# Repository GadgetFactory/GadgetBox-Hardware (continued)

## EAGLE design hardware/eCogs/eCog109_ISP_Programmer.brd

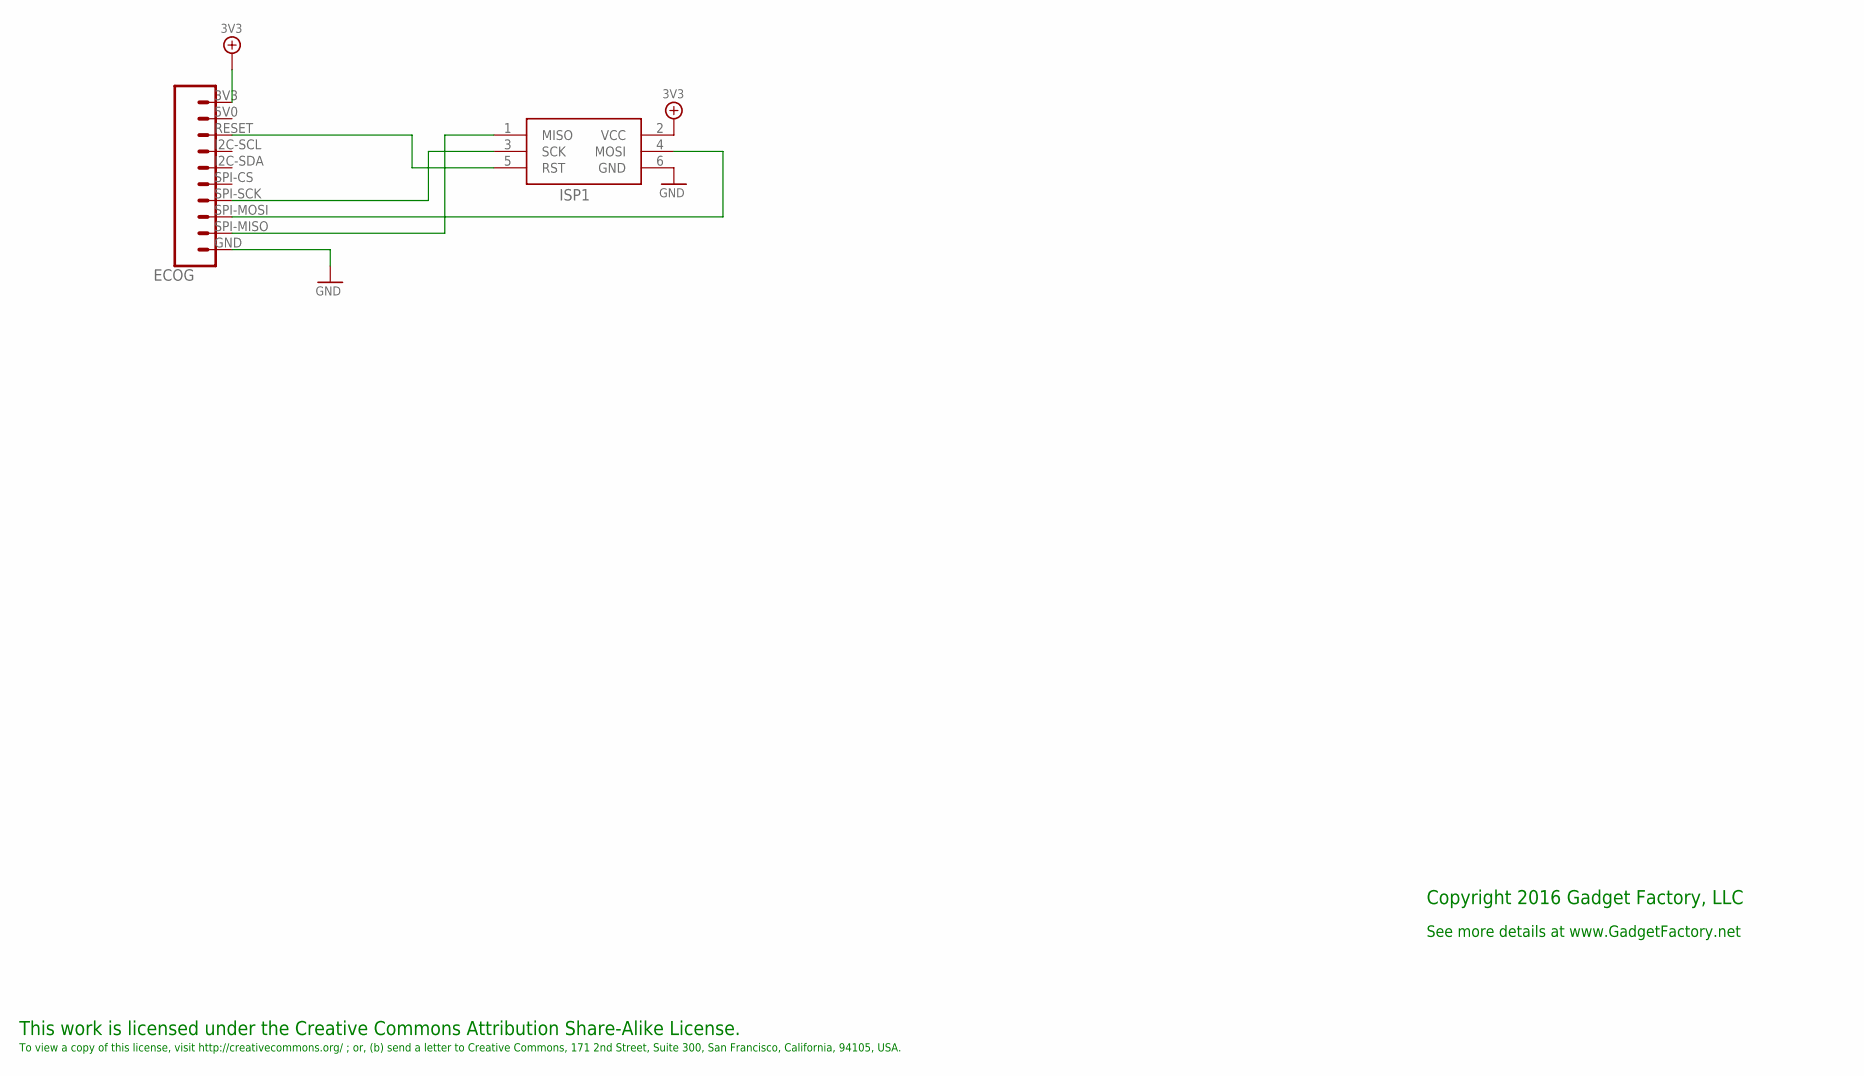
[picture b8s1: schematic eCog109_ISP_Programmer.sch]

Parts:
ECOG: ECOG_BUSES_ROWTHROUGHHOLE; ECOG_BUSES_TH
ISP1: AVRISP-6; AVRISP

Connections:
3V3: ECOG.3V3, ISP1.2 (VCC)
GND: ECOG.GND, ISP1.6 (GND)
unnamed: ECOG.SPI-MISO, ISP1.1 (MISO)
unnamed: ECOG.SPI-SCK, ISP1.3 (SCK)
unnamed: ECOG.RESET (RSV), ISP1.5 (RST)
unnamed: ECOG.SPI-MOSI, ISP1.4 (MOSI)

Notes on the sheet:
This work is licensed under the Creative Commons Attribution Share-Alike License.
To view a copy of this license, visit http://creativecommons.org/ ; or, (b) send a letter to Creative Commons, 171 2nd Street, Suite 300, San Francisco, California, 94105, USA.
Copyright 2016 Gadget Factory, LLC
See more details at www.GadgetFactory.net

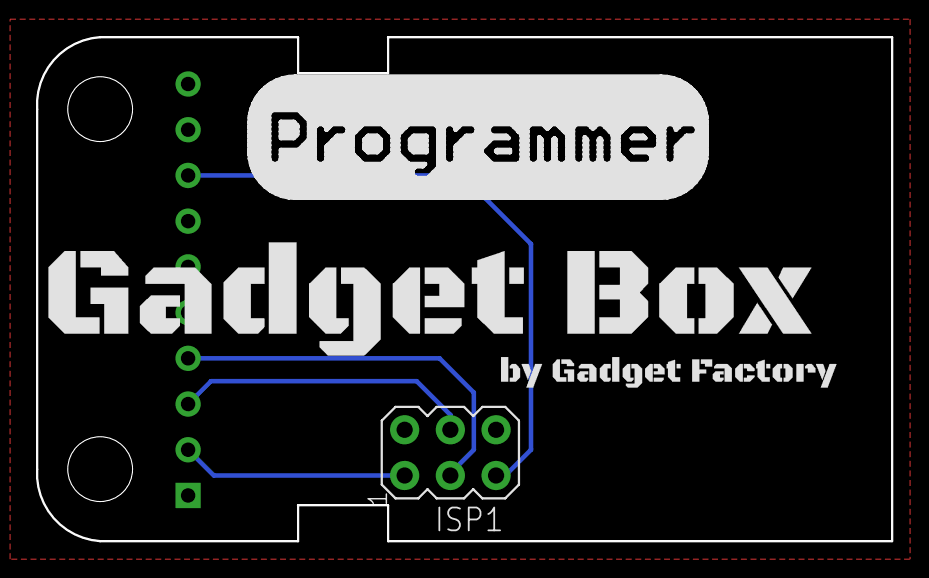
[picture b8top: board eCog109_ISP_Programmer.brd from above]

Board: 2 copper layers, 47.5 x 28.0 mm, 3 parts (0 on the bottom side), 6 nets.

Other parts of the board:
U$1: GADGETBOX_TEXT
